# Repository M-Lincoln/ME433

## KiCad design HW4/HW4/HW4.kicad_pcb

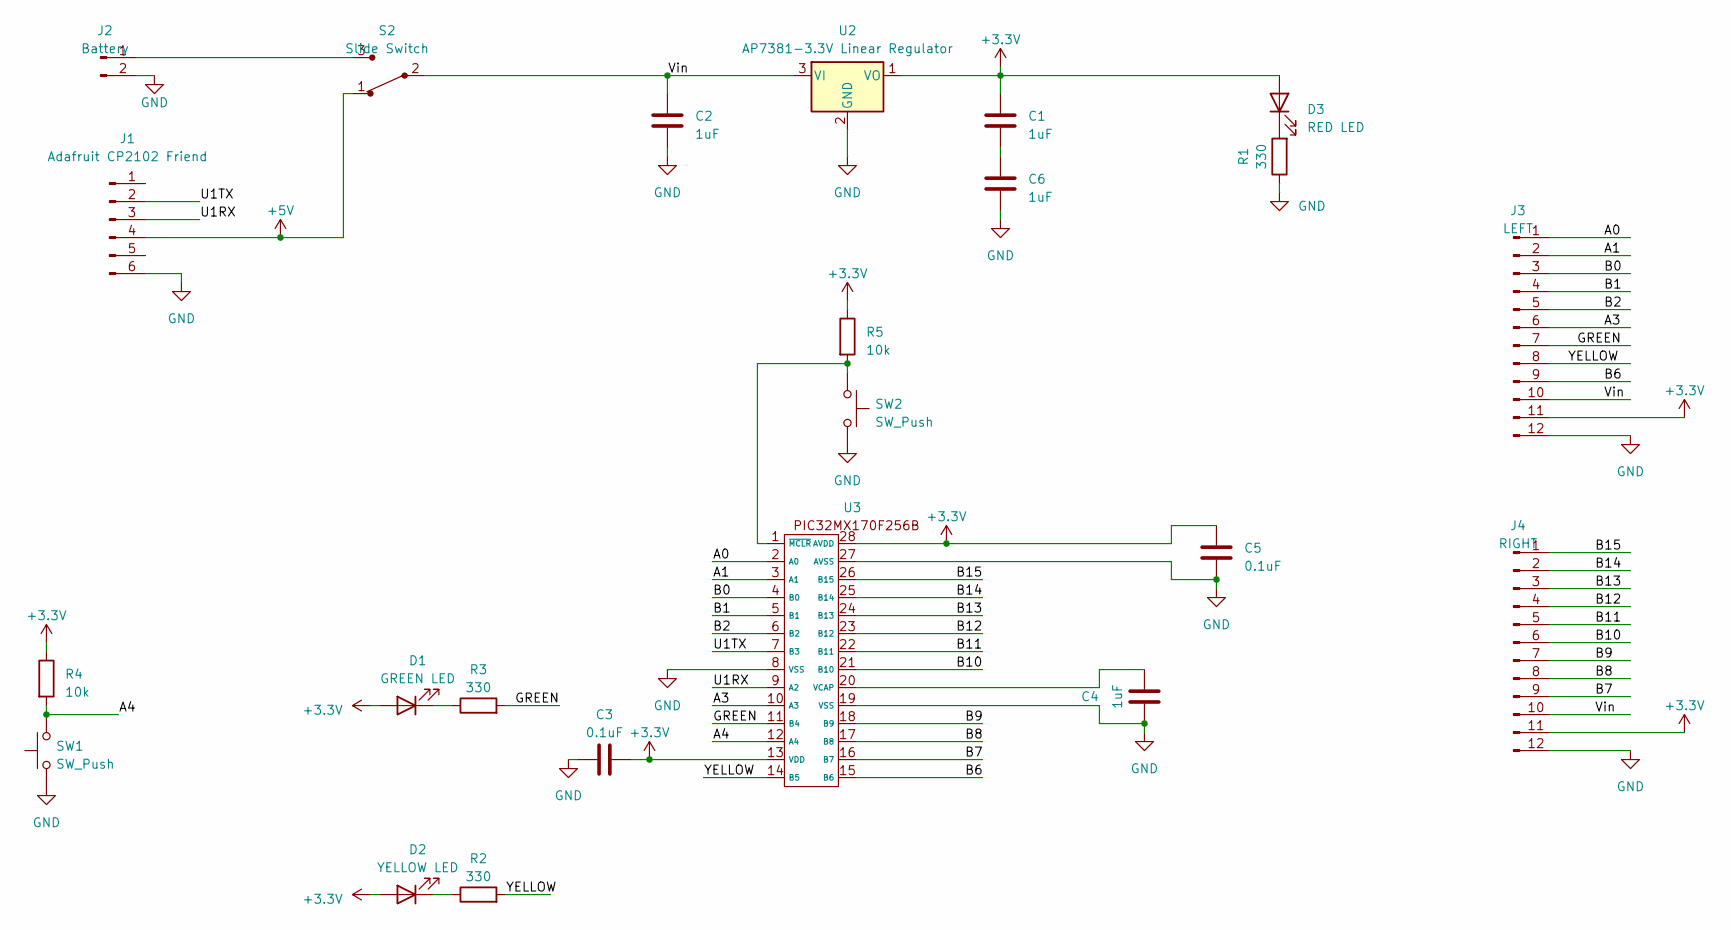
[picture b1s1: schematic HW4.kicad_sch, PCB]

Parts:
C1, C2, C4, C6: 1uF; C_Disc_D5.1mm_W3.2mm_P5.00mm
C3, C5: 0.1uF; C_Disc_D3.4mm_W2.1mm_P2.50mm
D1: GREEN LED; LED_D3.0mm
D2: YELLOW LED; LED_D3.0mm
D3: RED LED; LED_D3.0mm
J1: Adafruit CP2102 Friend; PinSocket_1x06_P2.54mm_Vertical
J2: Battery; PinSocket_1x02_P2.54mm_Vertical
J3: LEFT; PinSocket_1x12_P2.54mm_Vertical
J4: RIGHT; PinSocket_1x12_P2.54mm_Vertical
R1, R2, R3: 330; R_Axial_DIN0207_L6.3mm_D2.5mm_P7.62mm_Horizontal
R4, R5: 10k; R_Axial_DIN0207_L6.3mm_D2.5mm_P7.62mm_Horizontal
S2: Slide Switch; slideswitch; MPN EG1218; Digi-Key_PN EG1903-ND
SW1, SW2: SW_Push; push_button
U2: AP7381-3.3V Linear Regulator; TO-92_Inline
U3: DIP-28_W7.62mm_LongPads

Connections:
+3.3V: C1.1, C3.2, C5.2, D1.2 (A), D2.2 (A), D3.2 (A), J3.11, J4.11, R4.1, R5.1, U2.1 (VO), U3.13 (VDD), U3.28 (AVDD)
+5V: J1.4, S2.1
/A0: J3.1, U3.2 (A0)
/A1: J3.2, U3.3 (A1)
/A3: J3.6, U3.10 (A3)
/A4: R4.2, SW1.2, U3.12 (A4)
/B0: J3.3, U3.4 (B0)
/B1: J3.4, U3.5 (B1)
/B2: J3.5, U3.6 (B2)
/B6: J3.9, U3.15 (B6)
/B7: J4.9, U3.16 (B7)
/B8: J4.8, U3.17 (B8)
/B9: J4.7, U3.18 (B9)
/B10: J4.6, U3.21 (B10)
/B11: J4.5, U3.22 (B11)
/B12: J4.4, U3.23 (B12)
/B13: J4.3, U3.24 (B13)
/B14: J4.2, U3.25 (B14)
/B15: J4.1, U3.26 (B15)
/GREEN: J3.7, R3.2, U3.11 (B4)
/U1RX: J1.3, U3.9 (A2)
/U1TX: J1.2, U3.7 (B3)
/Vin: C2.1, J3.10, J4.10, S2.2, U2.3 (VI)
/YELLOW: J3.8, R2.2, U3.14 (B5)
GND: C2.2, C3.1, C4.1, C5.1, C6.2, J1.6, J2.2, J3.12, J4.12, R1.1, SW1.1, SW2.2, U2.2 (GND), U3.8 (VSS), U3.19 (VSS), U3.27 (AVSS)
unnamed: C1.2, C6.1
unnamed: D1.1 (K), R3.1
unnamed: D2.1 (K), R2.1
unnamed: D3.1 (K), R1.2
unnamed: J2.1, S2.3
unnamed: C4.2, U3.20 (VCAP)
unnamed: R5.2, SW2.1, U3.1 (~MCLR)

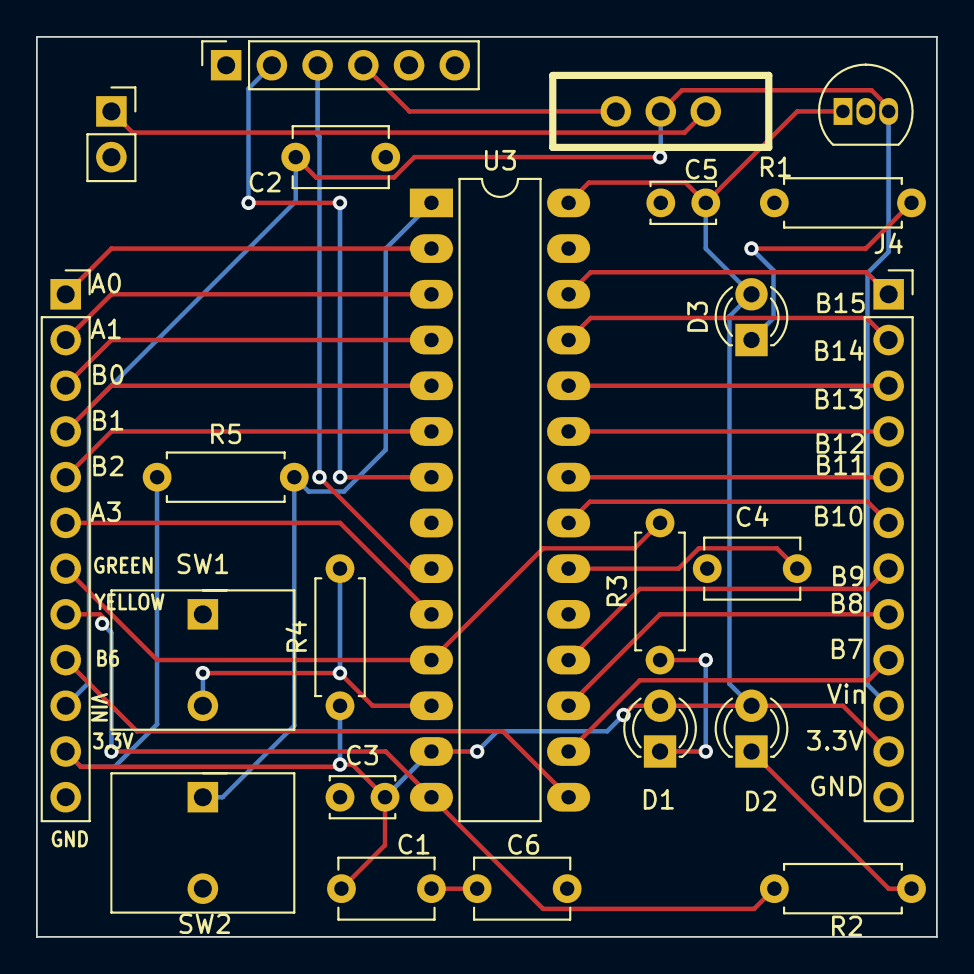
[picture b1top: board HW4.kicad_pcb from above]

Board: 2 copper layers, 50.0 x 50.0 mm, 23 parts (0 on the bottom side), 32 nets.

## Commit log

2023-04-03 HW2 additions
2023-04-04 HW2 Completion
2023-04-04 Submission documents
2023-04-05 HW3 setup
2023-04-05 HW3.X created and edit template.c
2023-04-05 Finishing up HW3
2023-04-05 link to HW3 code
2023-04-14 HW4 KiCAD schematic
2023-04-22 HW4 Finish
2023-04-22 rearrange folder
2023-04-28 HW5 and HW6 start
2023-04-28 Final HW5
2023-04-28 HW6-blinking GP7
2023-04-28 upload oscilloscope reading for hw5
2023-04-30 Finish HW6
2023-04-30 HW6 Submission
2023-05-07 HW7 Complete
2023-05-10 Blink LED and 1 pixel on OLED screen
2023-05-10 drawChar() function works
2023-05-10 Completed DrawString()fnc/noah love letter
2023-05-11 Read accelerometer data to OLED screen
2023-05-11 Add demo video
2023-05-12 Finish HW9
2023-05-12 Neopixels light up and work
2023-05-12 Infinite Rainbow complete
2023-05-12 upload hw10 demo
2023-05-17 HW11 done
2023-05-26 HW14
2023-05-26 upload demo hw14
2023-06-06 Final Robot Updates
2023-06-08 HW16
